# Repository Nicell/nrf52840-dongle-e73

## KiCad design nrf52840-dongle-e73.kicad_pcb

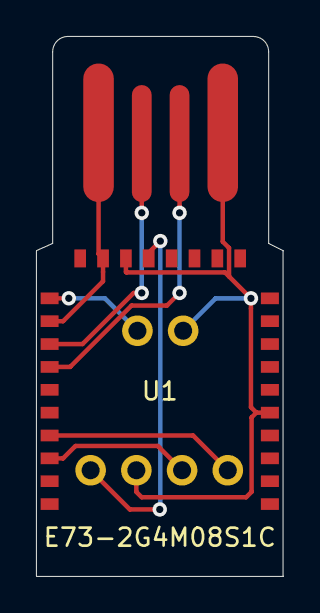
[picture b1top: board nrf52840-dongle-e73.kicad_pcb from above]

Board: 2 copper layers, 13.7 x 30.0 mm, 4 parts (1 on the bottom side), 8 nets.

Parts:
J1: Conn_01x04_Female; programmer-conn
J2: Conn_01x02_Female; reset-conn
J3: USB_A; usb-pcb
U1: E73-2G4M08S1C-52840; E73-2G4M08S1C-52840-NO-UNDER

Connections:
GND: J1.2, J2.2, J3.4, U1.5, U1.21
unnamed: J3.2, U1.29
unnamed: J3.3, U1.31
RESET: J2.1, U1.26
SWC: J1.3, U1.39
SWD: J1.4, U1.37
VBUS: J3.1, U1.23, U1.27
VCC: J1.1, U1.19

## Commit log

2020-07-29 Add KiCad files
2020-07-29 Remove reversability
